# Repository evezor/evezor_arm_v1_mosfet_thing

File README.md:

# evezor_arm_v1_mosfet_thing

This board has a few mosfets intended to be used for relays, small fans, lights and other small loads. 

It incorporates a gadgeteer port to work with the mainboard who's source can be found here: https://github.com/evezor/evezor_arm_v1_mainboard_V2

The source files for this board can be found here: https://github.com/evezor/evezor_arm_v1_mosfet_thing

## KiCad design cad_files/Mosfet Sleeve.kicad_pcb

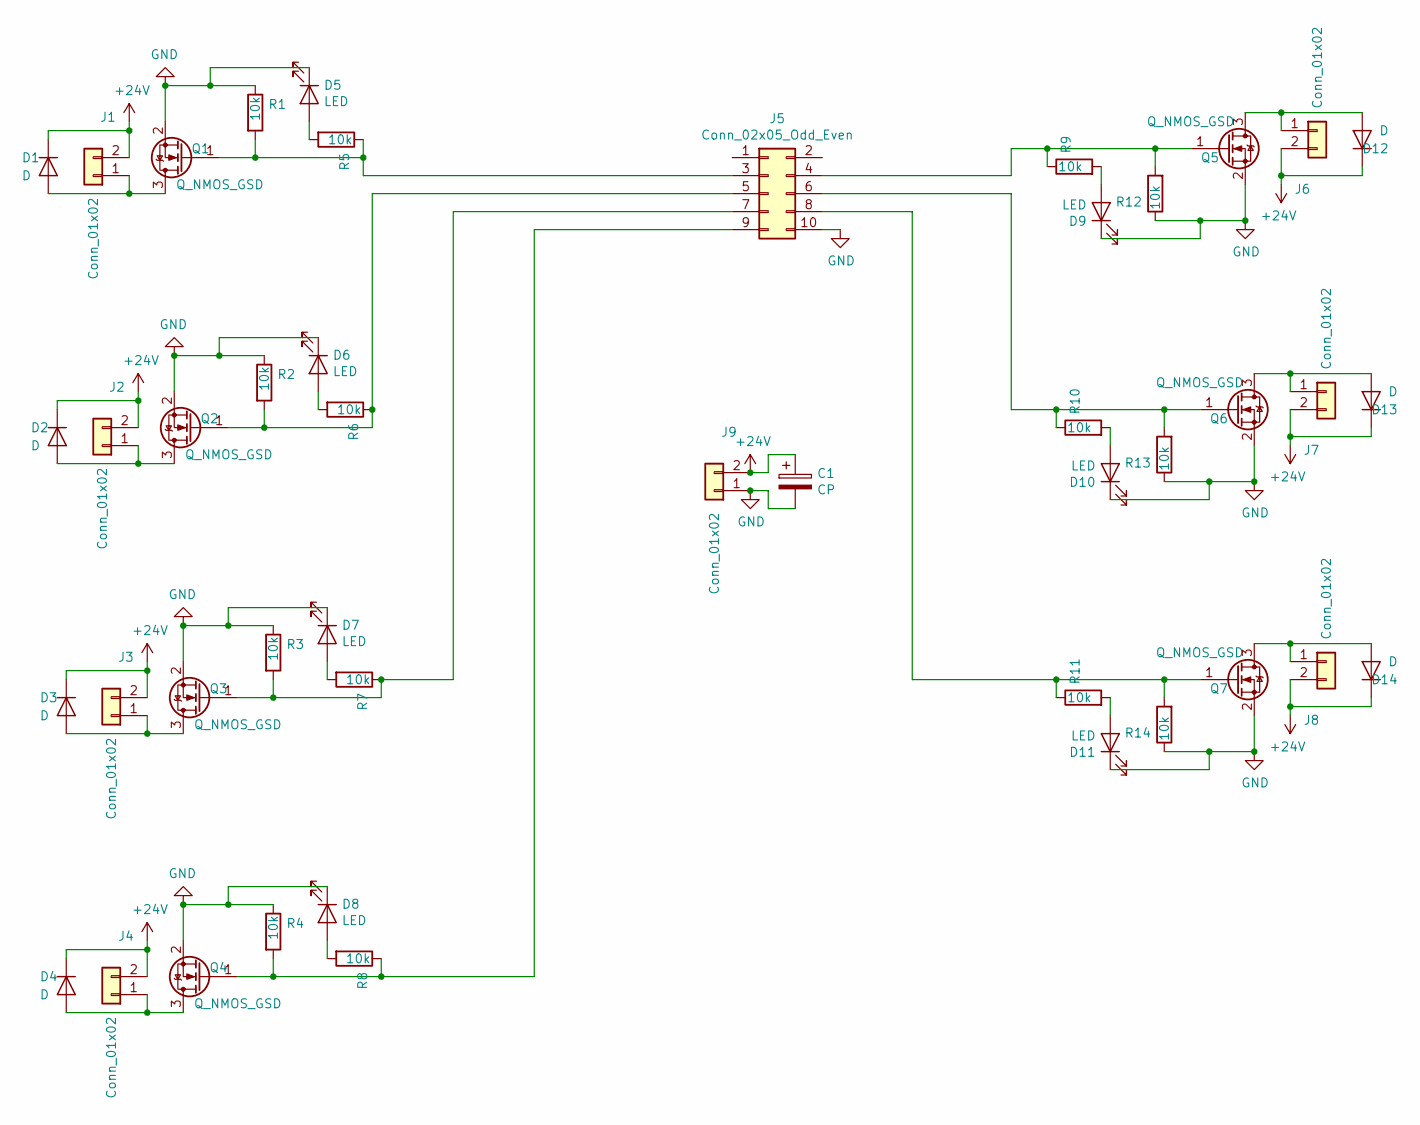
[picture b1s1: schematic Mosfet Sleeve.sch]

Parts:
C1: CP; CP_Elec_8x6.2
D1, D2, D3, D4, D12, D13, D14: D; D_DO-35_SOD27_P5.08mm_Vertical_AnodeUp
D5, D6, D7, D8, D9, D10, D11: LED; LED_0805_2012Metric
J1, J2, J3, J4, J6, J7, J8, J9: Conn_01x02; CONN_ON_SHORE_2x_15A
J5: Conn_02x05_Odd_Even; 10_PIN_IDC
Q1, Q2, Q3, Q4, Q5, Q6, Q7: Q_NMOS_GSD; SOT-23
R1, R2, R3, R4, R5, R6, R7, R8, R9, R10, R11, R12, R13, R14: 10k; R_0603_1608Metric

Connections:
+24V: C1.1, D1.1 (K), D2.1 (K), D3.1 (K), D4.1 (K), D12.1 (K), D13.1 (K), D14.1 (K), J1.2, J2.2, J3.2, J4.2, J6.2, J7.2, J8.2, J9.2
GND: C1.2, D5.1 (K), D6.1 (K), D7.1 (K), D8.1 (K), D9.1 (K), D10.1 (K), D11.1 (K), J5.10, J9.1, Q1.2 (S), Q2.2 (S), Q3.2 (S), Q4.2 (S), Q5.2 (S), Q6.2 (S), Q7.2 (S), R1.1, R2.1, R3.1, R4.1, R12.1, R13.1, R14.1
unnamed: D1.2 (A), J1.1, Q1.3 (D)
unnamed: D2.2 (A), J2.1, Q2.3 (D)
unnamed: D3.2 (A), J3.1, Q3.3 (D)
unnamed: D4.2 (A), J4.1, Q4.3 (D)
unnamed: D5.2 (A), R5.2
unnamed: D6.2 (A), R6.2
unnamed: D7.2 (A), R7.2
unnamed: D8.2 (A), R8.2
unnamed: D9.2 (A), R9.2
unnamed: D10.2 (A), R10.2
unnamed: D11.2 (A), R11.2
unnamed: D12.2 (A), J6.1, Q5.3 (D)
unnamed: D13.2 (A), J7.1, Q6.3 (D)
unnamed: D14.2 (A), J8.1, Q7.3 (D)
unnamed: J5.3, Q1.1 (G), R1.2, R5.1
unnamed: J5.4, Q5.1 (G), R9.1, R12.2
unnamed: J5.5, Q2.1 (G), R2.2, R6.1
unnamed: J5.6, Q6.1 (G), R10.1, R13.2
unnamed: J5.7, Q3.1 (G), R3.2, R7.1
unnamed: J5.8, Q7.1 (G), R11.1, R14.2
unnamed: J5.9, Q4.1 (G), R4.2, R8.1

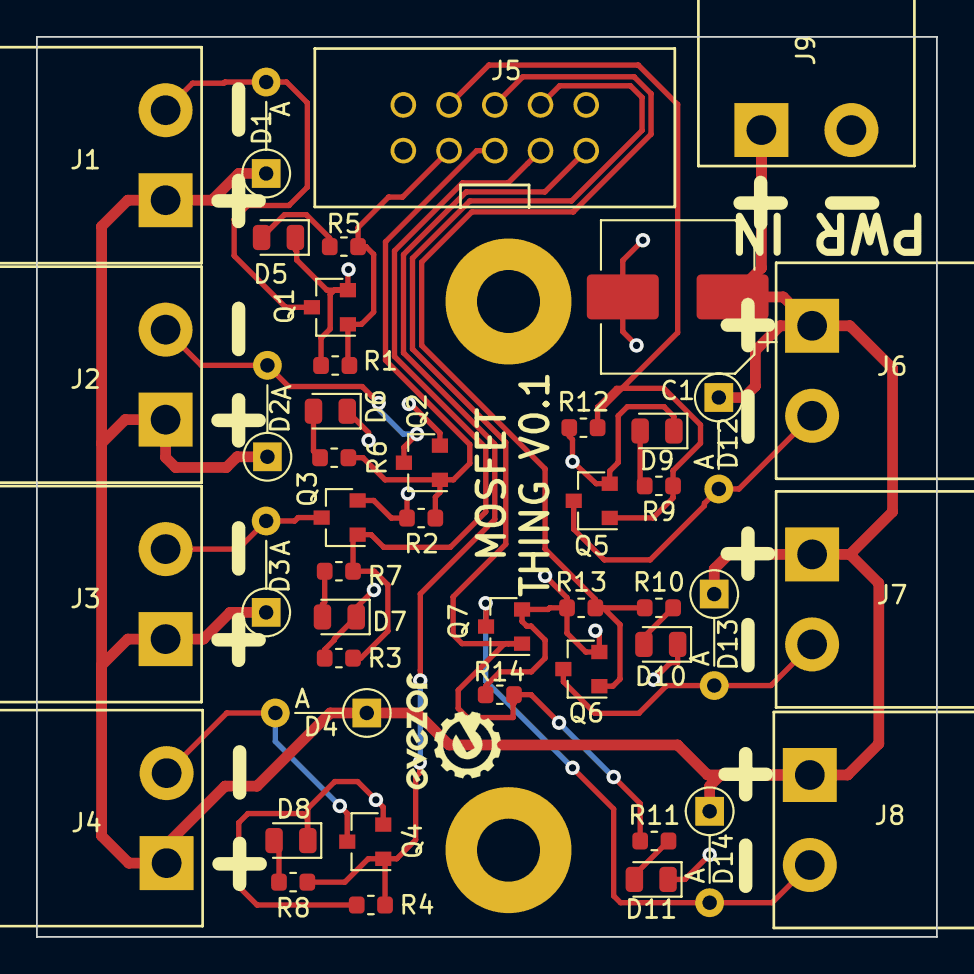
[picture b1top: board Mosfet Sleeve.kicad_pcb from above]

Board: 2 copper layers, 50.0 x 50.0 mm, 45 parts (0 on the bottom side), 23 nets.

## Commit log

2023-10-12 init
